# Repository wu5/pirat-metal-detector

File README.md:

PIRAT (Pulse Induction) metal detector

Импульсный металлоискатель ПИРАТ

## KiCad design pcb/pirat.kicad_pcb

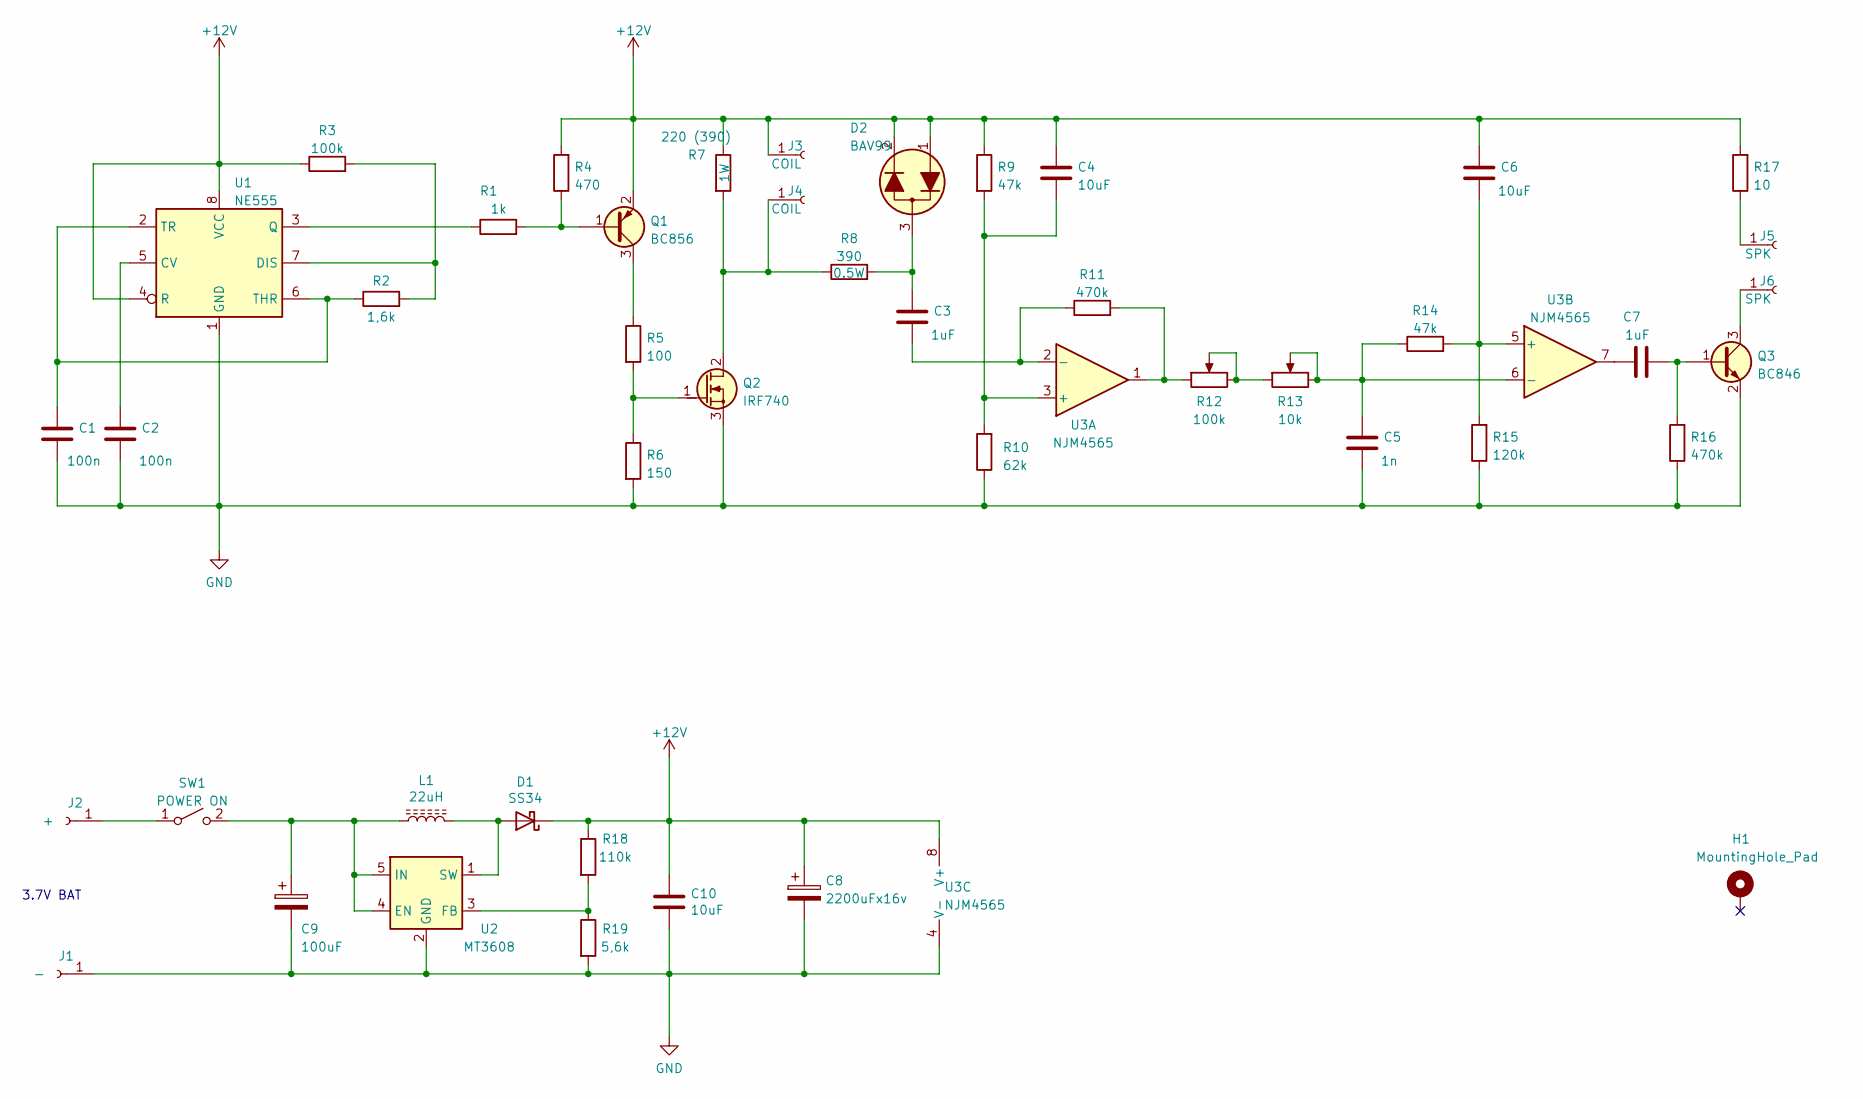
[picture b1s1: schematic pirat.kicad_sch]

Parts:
C1, C2: 100n; C_Rect_L7.2mm_W2.5mm_P5.00mm_FKS2_FKP2_MKS2_MKP2
C3, C7: 1uF; C_1206
C4, C6, C10: 10uF; C_1206
C5: 1n; C_1206
C8: 2200uFx16v; CP_Radial_D10.0mm_P5.00mm
C9: 100uF; C_1206
D1: SS34; D_SMA
D2: BAV99; SOT-23
H1: MountingHole_Pad; MountingHole_3mm
J1: -; TestPoint_THTPad_D3.0mm_Drill1.5mm
J2: +; TestPoint_THTPad_D3.0mm_Drill1.5mm
J3, J4: COIL; TestPoint_THTPad_D3.0mm_Drill1.5mm
J5, J6: SPK; TestPoint_THTPad_D2.5mm_Drill1.2mm
L1: 22uH; Inductor_SMD_CD74R
Q1: BC856; SOT-23
Q2: IRF740; TO-220-3_Vertical_GDS
Q3: BC846; SOT-23
R1: 1k; R_1206
R2: 1,6k; R_1206
R3: 100k; R_1206
R4: 470; R_1206
R5: 100; R_1206
R6: 150; R_1206
R7: 220 (390); R_2512
R8: 390; R_2512
R9, R14: 47k; R_1206
R10: 62k; R_1206
R11, R16: 470k; R_1206
R12: 100k; Potentiometer_16mm_Hole
R13: 10k; Potentiometer_16mm_Hole
R15: 120k; R_1206
R17: 10; R_1206
R18: 110k; R_1206
R19: 5,6k; R_1206
SW1: POWER ON; Switch_SPDT_Hole
U1: NE555; SOIC-8_3.9x4.9mm_P1.27mm
U2: MT3608; SOT-23-6
U3: NJM4565; SOIC-8

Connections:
+12V: C4.2, C6.2, C8.1, C10.2, D1.1 (K), D2.1 (A), D2.2 (K), J3.1, Q1.2 (E), R3.1, R4.2, R7.1, R9.1, R17.2, R18.1, U1.4 (R), U1.8 (VCC), U3.8 (V+)
GND: C1.1, C2.2, C5.1, C8.2, C9.2, C10.1, J1.1, Q2.3 (S), Q3.2 (E), R6.2, R10.1, R15.1, R16.1, R19.2, U1.1 (GND), U2.2 (GND), U3.4 (V-)
unnamed: C7.2, U3.7
unnamed: D1.2 (A), L1.2, U2.1 (SW)
unnamed: C3.2, D2.3 (C), R8.2
unnamed: J2.1, SW1.1 (A)
unnamed: J4.1, Q2.2 (D), R7.2, R8.1
unnamed: J5.1, R17.1
unnamed: J6.1, Q3.3 (C)
unnamed: Q1.1 (B), R1.2, R4.1
unnamed: Q1.3 (C), R5.1
unnamed: Q2.1 (G), R5.2, R6.1
unnamed: C7.1, Q3.1 (B), R16.2
unnamed: R11.2, R12.1, U3.1
unnamed: R12.2, R12.3, R13.1
unnamed: C9.1, L1.1, SW1.2 (B), U2.4 (EN), U2.5 (IN)
unnamed: C2.1, U1.5 (CV)
unnamed: R2.2, R3.2, U1.7 (DIS)
unnamed: R1.1, U1.3 (Q)
unnamed: C1.2, R2.1, U1.2 (TR), U1.6 (THR)
unnamed: R18.2, R19.1, U2.3 (FB)
unnamed: C4.1, R9.2, R10.2, U3.3 (+)
unnamed: C3.1, R11.1, U3.2 (-)
unnamed: C6.1, R14.2, R15.2, U3.5 (+)
unnamed: C5.2, R13.2, R13.3, R14.1, U3.6 (-)

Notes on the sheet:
3.7V BAT

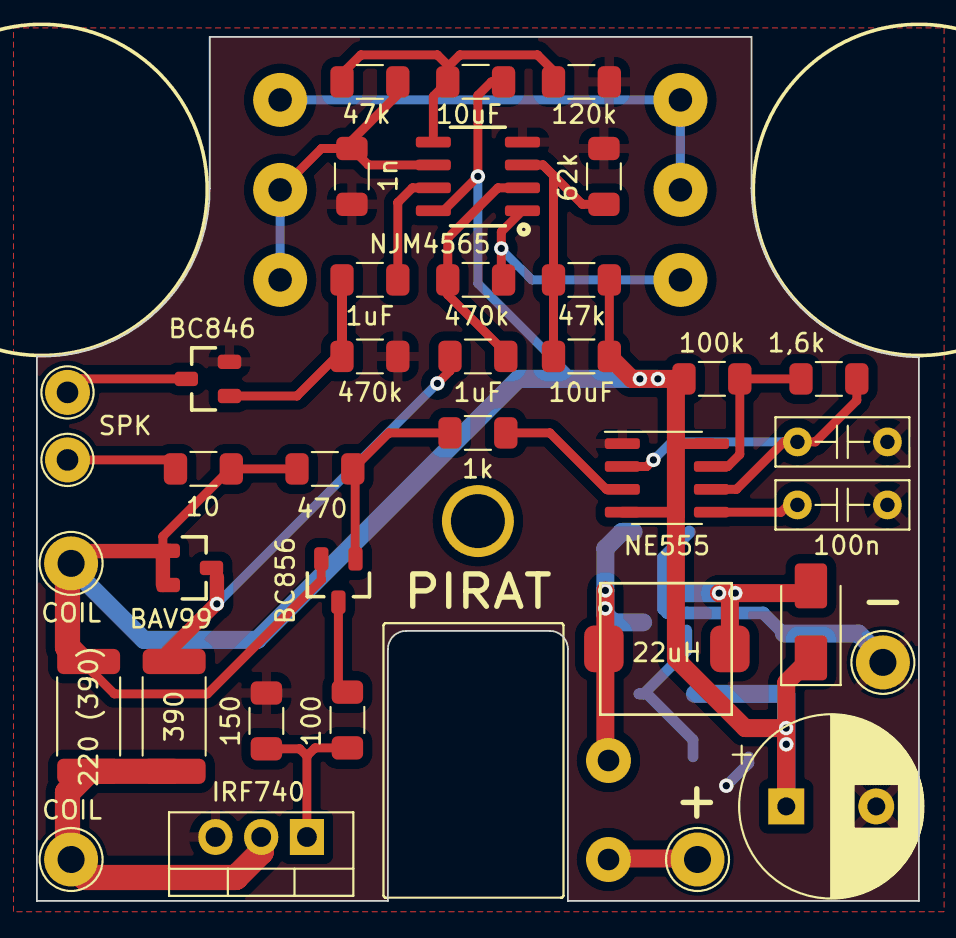
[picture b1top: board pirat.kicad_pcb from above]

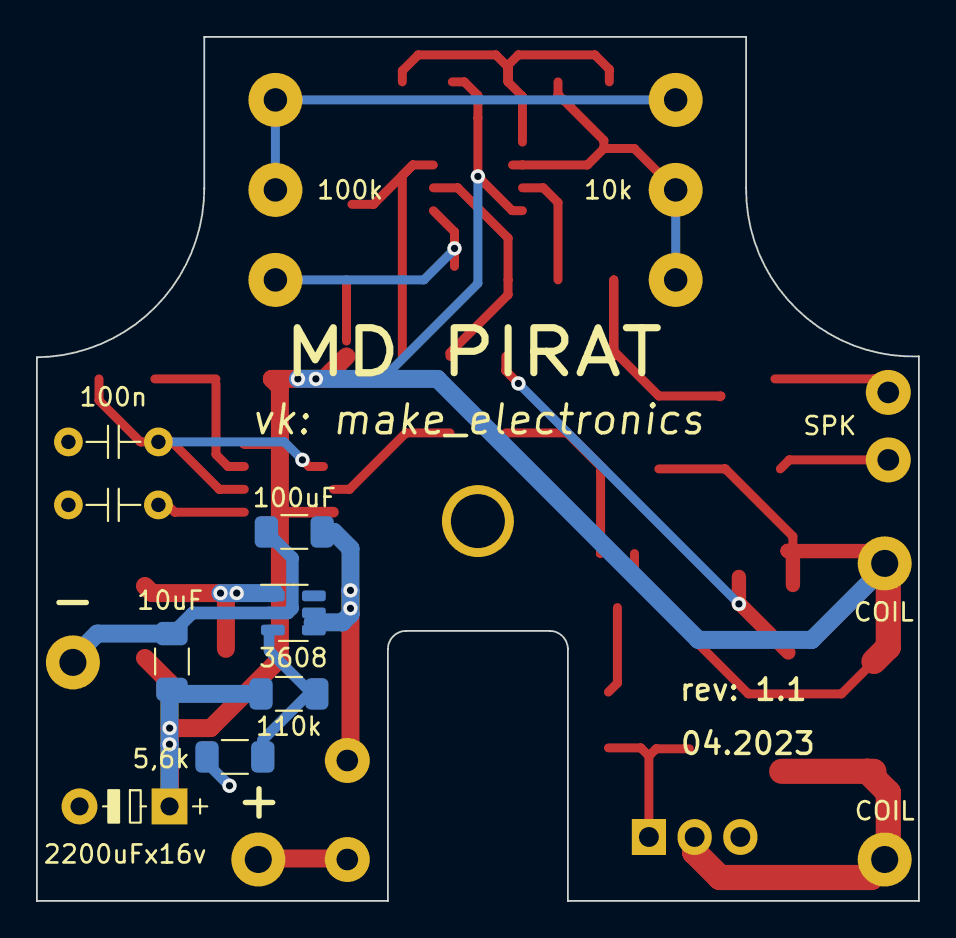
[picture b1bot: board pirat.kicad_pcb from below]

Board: 2 copper layers, 49.0 x 48.0 mm, 46 parts (5 on the bottom side), 25 nets.

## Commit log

2023-04-20 move
